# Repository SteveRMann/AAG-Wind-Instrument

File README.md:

# AAG Wind Instrument
I acquired a brand new AAG Wind Instrument that had virtually no documentation.   Most of the links on the web were broken, so I had little to go on.
The schematic that I found is almost exactly the same as my device and was enough information to get started.

I also found Arduino libraries for the three DS devices on the PCB at https://github.com/jbechter.

## Versions
(From http://sheepdogsoftware.co.uk/sc3wmw.htm#gotoVer)
The wind speed/ direction sensor is "Version 3". Earlier versions used different electronics for sensing the wind direction and You can tell one from the other by
--the markings on the PCB:"Ceprei version 2" (Yes: two)
or
--By using an i2c Scanner. If there is a DS2450 (ID ends hex 20), the device is version 3.

## Getting Chip ID's
Each 1-wire chip has it's own unique 64-bit serial number. The program needs to know the serial numbers. I wrote an Arduino sketch "one_wire_address_finder" which revelaled three DS chips on the 1-wire network. 
The DS2450 (1-Wire Quad A/D Converter) handles the wind direction
The DS18S20 (1-Wire Temperature Digital Serial Sensor) provides the temperature. (Works just like an 18B20, but 4X the cost).
And the DS2423 (4kbit 1-Wire RAM with Counter) determines the wind speed.

Sketch: *one_wire_address_finder* found these chips on my instrument:
- address : 0x2027BF00000000FC  //DS2450 4-channel (ADC, A/D converter)
- address : 0x10744E1B0008002E  //DS1920, DS1820, DS18S20 (Temperature with alarm trips)
- address : 0x1DF6F90000000056  //DS2423 (4Kb NV RAM memory with external counters)

The RJ11 green wire is the 1-wire bus, the red wire is ground.

## DS2450
### Wind Direction
The version 3 AAG wind direction sensor implements a delightfully clever way to encode the shaft's position.
The wind direction relies on 4 ADCs to sense the state of the 8 reed switches. No adjacent reed switches are on the same ADC. When no magnet is near one of the switches, the ADC it is connected to "sees" 5 volts. When a magnet is near one of the switches, the ADC "sees" either 0 volts or about 2.5 volts, depending on which switch the magnet is near. For a given ADC, only one switch can be closed at a given moment. Each ADC can "watch" two switches because resistors in the circuits allow the three possible voltages on each ADC monitored line.

Just to fill in the detail: When a switch is open, the input to the ADC is connected to 5v through a resistor. In one case, the reed switch connects the ADC directly to 0v, so when the switch closes, the ADC "sees" 0 volts. In the other case, the reed switch connects the ADC to 0 volts through a second resistor. This, in combination with the resistor connecting the ADC to 5 volts results in the ADC "seeing" about 2.5 volts.

Thus, the ADC "sees" a high, or low, or "medium" voltage.

## DS2423
### Wind Speed
Two magnets mounted on a second rotor attached to the wind cups axle operate a reed switch connected to the DS2423 (4kbit 1-Wire RAM with Counter) which provides a unique identification for this sensor with its 1-Wire serial number. One magnet is mounted in each of the two outermost holes of the rotor. This provides two counts per revolution which improves response at low wind speeds. It also provides rotational balance to the rotor, which becomes important with increasing wind speed, as the rotor can reach 2400 rpm in 160 km/h winds. The DS2423 keeps track of the total number of revolutions the wind cups make and provides the data to the bus master on demand. The chip contains two 232 bit counters and can be powered for ten years with a small Lithium battery, however, here power for the counter chip comes from D1, D2 and C1,  which form a half wave rectifier that “steals” power from the data line. The DS2423 can only be reset to zero when this “parasite power” is lost. Wind speed is calculated by the program taking the difference between two counts of the counter used. One count generated before and the other after a clocked interval. The output is currently given in rpm. This later needs to be converted to m/s or km/h.

# Home Assistant
<h3 align="center">Interfacing with Home Assistant</h3>

Home Assistant sees the Windstation over MQTT.
In 'mqtt.yaml':

```yaml
 sensor:
    - name: "Windstation Temperature C"
      state_topic: "windStation/celsius"
      unit_of_measurement: "°C"
            
    - name: "Windstation Temperature F"
      state_topic: "windStation/fahrenheit"
      unit_of_measurement: "°F"
            
    - name: "Windstation Humidity"
      state_topic: "windStation/humidity"
      unit_of_measurement: "%"      
      
    - name: "Windstation Windspeed"
      state_topic: "windStation/speed"
      unit_of_measurement: "MPH"      
      
    - name: "Windstation Wind Direction"
      state_topic: "windStation/direction"
            
    - name: "Windstation Pyranometer"
      state_topic: "windStation/pyranometer"
      unit_of_measurement: "W/m^2"     
```

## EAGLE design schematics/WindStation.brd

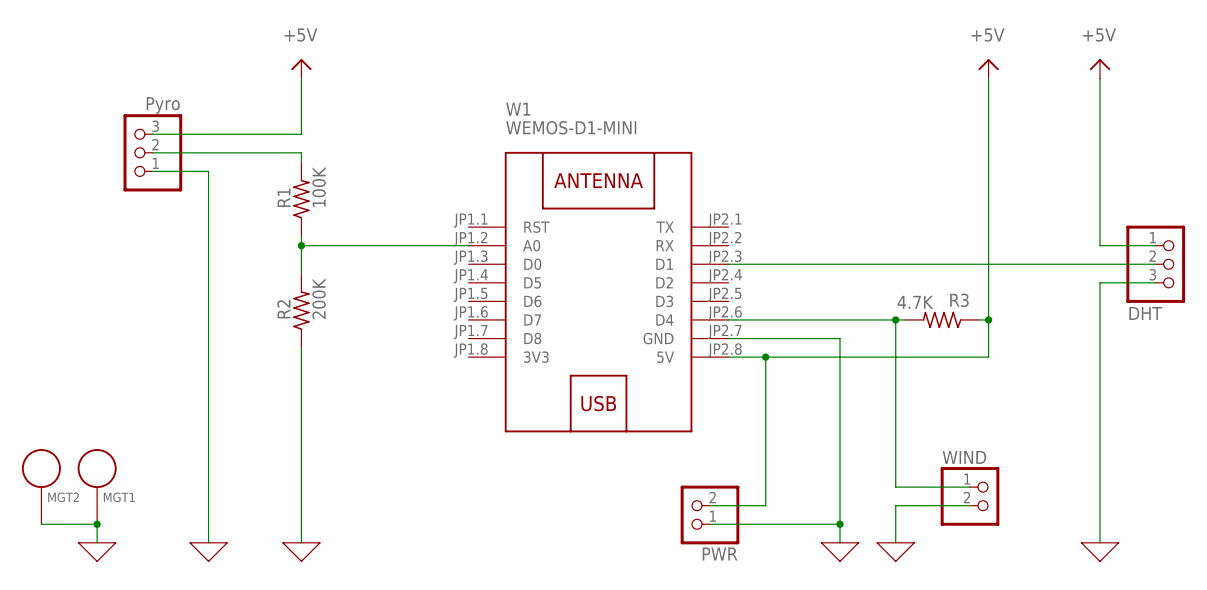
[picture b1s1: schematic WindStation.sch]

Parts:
DHT: DHT; 1X03
JP1: Pyro; 1X03
MGT1, MGT2: BEAGLEBONEBLACK_MOUNTING_HOLE
PWR: PINHD-1X2; 1X02
R1: 100K; 0207/10
R2: 200K; 0207/10
R3: 4.7K; 0207/10
W1: WEMOS-D1-MINI
WIND: PINHD-1X2; 1X02

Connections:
0: DHT.3, JP1.1, MGT1.P$1, MGT2.P$1, PWR.1, R2.1, W1.JP2.7 (GND), WIND.2
3V3: W1.JP1.8 (3V3)
unnamed: JP1.2, R1.2
unnamed: R1.1, R2.2, W1.JP1.2 (A0)
unnamed: R3.2, W1.JP2.6 (D4), WIND.1
unnamed: DHT.2, W1.JP2.3 (D1)
VCC: DHT.1, JP1.3, PWR.2, R3.1, W1.JP2.8 (5V)

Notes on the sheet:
+5V

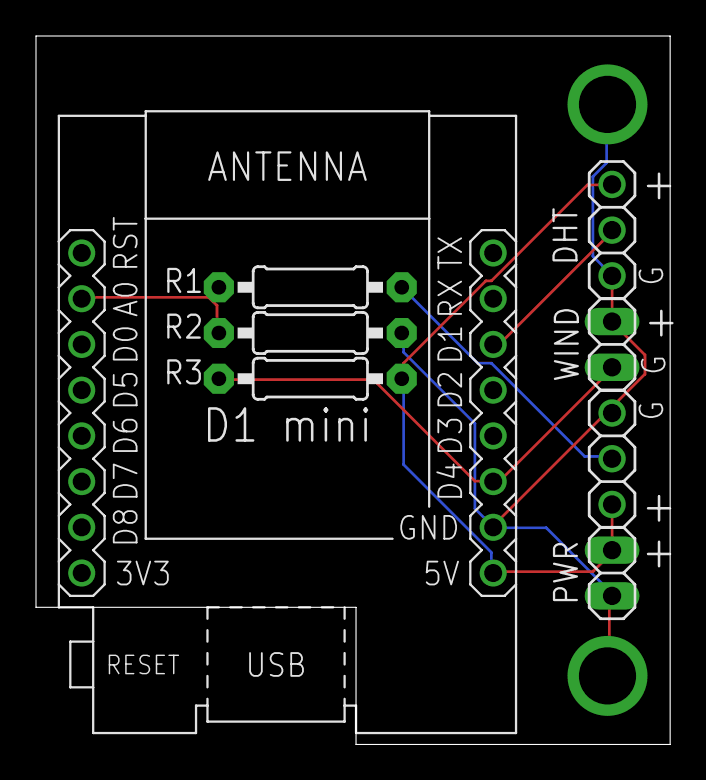
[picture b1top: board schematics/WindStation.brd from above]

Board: 2 copper layers, 35.2 x 39.4 mm, 10 parts (0 on the bottom side), 6 nets.

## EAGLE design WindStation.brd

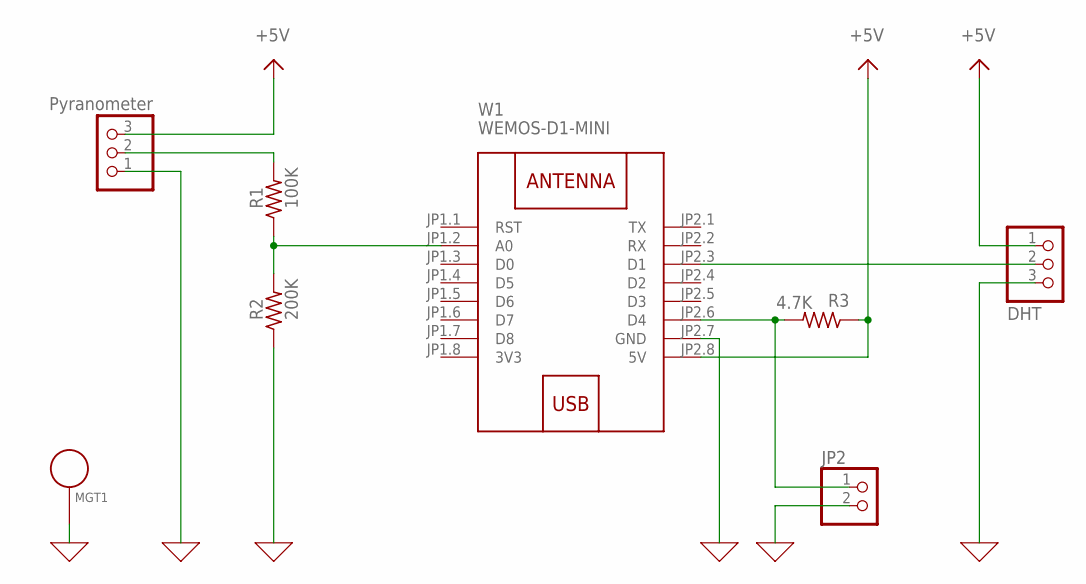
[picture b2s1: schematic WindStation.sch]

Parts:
JP1: Pyranometer; 1X03
JP2: PINHD-1X2; 1X02
JP3: DHT; 1X03
MGT1: BEAGLEBONEBLACK_MOUNTING_HOLE
R1: 100K; 0207/10
R2: 200K; 0207/10
R3: 4.7K; 0207/10
W1: WEMOS-D1-MINI

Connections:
0: JP1.1, JP2.2, JP3.3, MGT1.P$1, R2.1, W1.JP2.7 (GND)
3V3: W1.JP1.8 (3V3)
unnamed: JP1.2, R1.2
unnamed: R1.1, R2.2, W1.JP1.2 (A0)
unnamed: JP2.1, R3.2, W1.JP2.6 (D4)
unnamed: JP3.2, W1.JP2.3 (D1)
VCC: JP1.3, JP3.1, R3.1, W1.JP2.8 (5V)

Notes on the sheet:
+5V

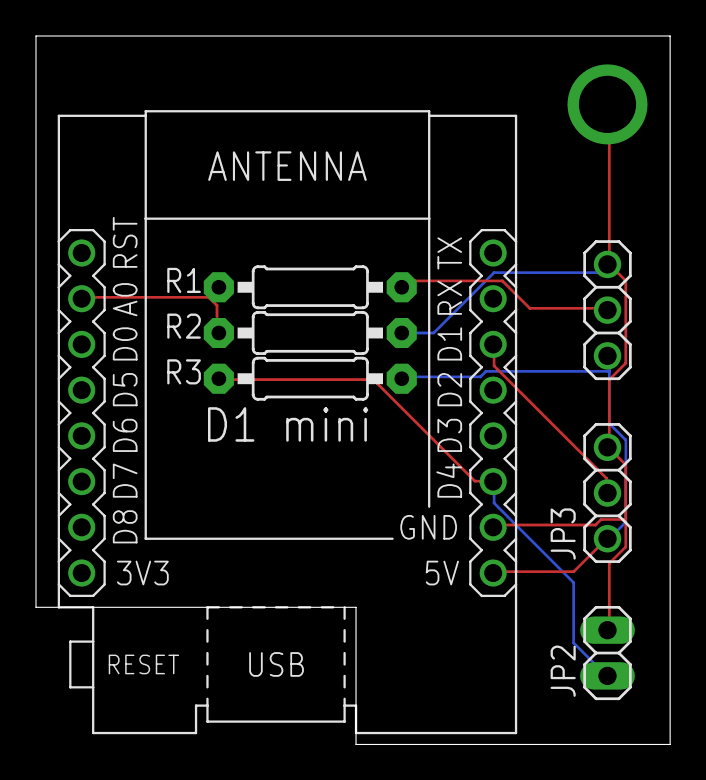
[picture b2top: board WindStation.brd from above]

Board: 2 copper layers, 35.2 x 39.4 mm, 8 parts (0 on the bottom side), 6 nets.

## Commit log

2022-05-19 Added src folder
2022-05-21 Added datalogger
2022-05-21 Added DS2423WindSpeedCalibration
2022-05-22 Added windStation.ino
2022-05-23 Added direction
2022-05-24 Added temperature, changed ticker.h to TickTwo.h
2022-05-24 Added image of AAG Wind Station
2022-05-25 Added humidity sensor
2022-05-27 Added humidity with temperature sensor
2022-05-27 Added a second test humidity library.
2022-06-07 Added DHT22 code
2022-06-14 Added DHT11 test code
2022-06-15 Integrated dht11 into the windStation.ino code.
2022-06-16 Added MQTT to publish sensors
2022-06-16 Added test for temperature error
2022-06-19 Added pyranometer
2022-06-19 Added schematics, added eagle to gitignore
2022-06-20 Create temp
2022-06-20 Moved schematics to the schematics folder
2022-06-23 Fixed handling the bad temperature readings.
2022-06-23 Changed DHT11 to DHT22
2022-06-27 changed topic variables
2022-06-27 Update schematic
2023-05-10 Update README.md
    Added Home Assistant notes to the readme.

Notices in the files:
parts and their libraries:
diy-modules: Released under the Creative Commons Attribution 4.0 International License: http://creativecommons.org/licenses/by/4.0
